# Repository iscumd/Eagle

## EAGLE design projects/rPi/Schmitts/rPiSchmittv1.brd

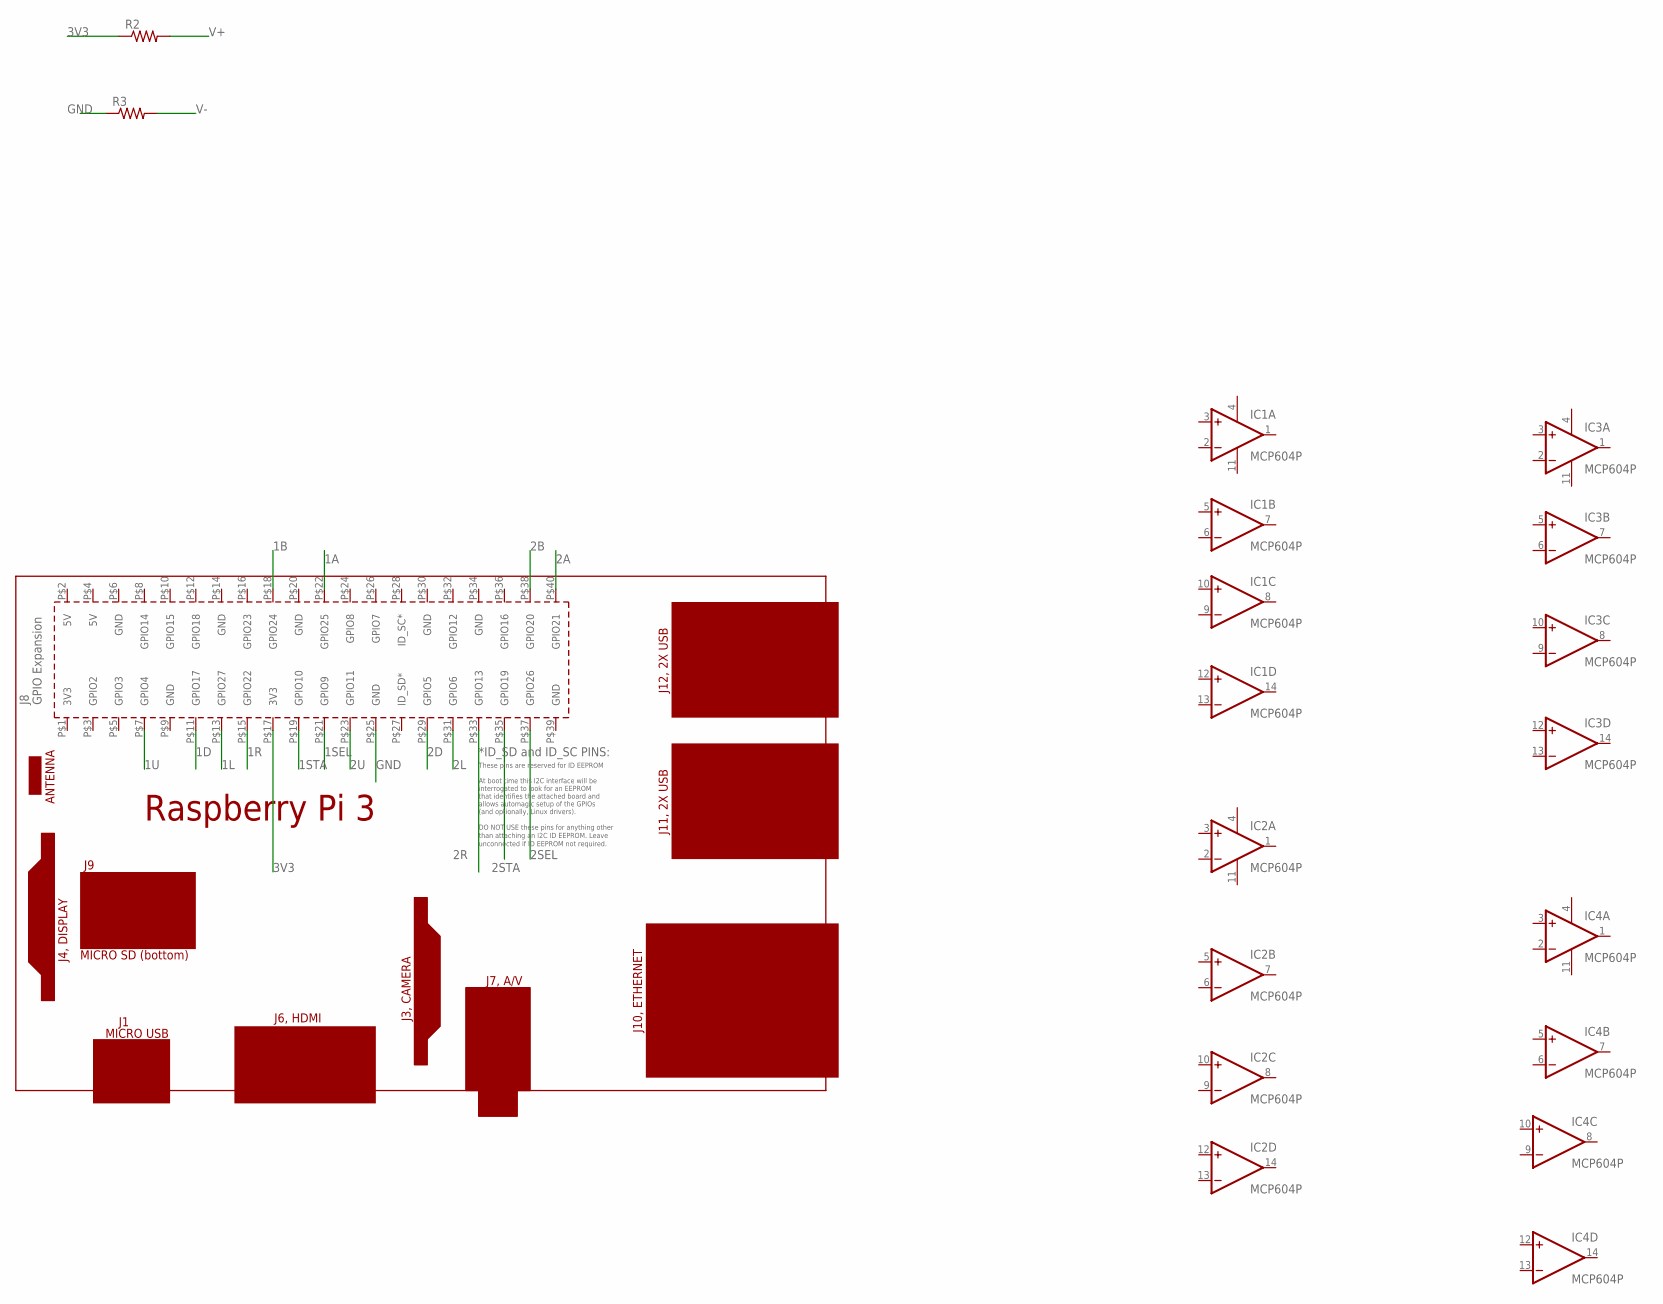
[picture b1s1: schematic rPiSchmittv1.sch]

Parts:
IC1, IC2, IC3, IC4: MCP604P; DIL14
PCB1: RPI3
R2, R3: RESISTOR0603-RES; 0603-RES

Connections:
1A: PCB1.P$22 (GPIO25)
1B: PCB1.P$18 (GPIO24)
1D: PCB1.P$11 (GPIO17)
1L: PCB1.P$13 (GPIO27)
1R: PCB1.P$15 (GPIO22)
1SEL: PCB1.P$21 (GPIO9)
1STA: PCB1.P$19 (GPIO10)
1U: PCB1.P$7 (GPIO4)
2A: PCB1.P$40 (GPIO21)
2B: PCB1.P$38 (GPIO20)
2D: PCB1.P$29 (GPIO5)
2L: PCB1.P$31 (GPIO6)
2R: PCB1.P$33 (GPIO13)
2SEL: PCB1.P$37 (GPIO26)
2STA: PCB1.P$35 (GPIO19)
2U: PCB1.P$23 (GPIO11)
3V3: PCB1.P$17 (3V3), R2.1
GND: PCB1.P$25 (GND), R3.1
V+: IC1.4 (V+), IC2.4 (V+), IC3.4 (V+), IC4.4 (V+), R2.2
V-: IC1.11 (V-), IC2.11 (V-), IC3.11 (V-), IC4.11 (V-), R3.2

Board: 2 copper layers, 8 parts (0 on the bottom side), 4 nets, no tracks yet.

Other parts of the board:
R1: 0603-RES

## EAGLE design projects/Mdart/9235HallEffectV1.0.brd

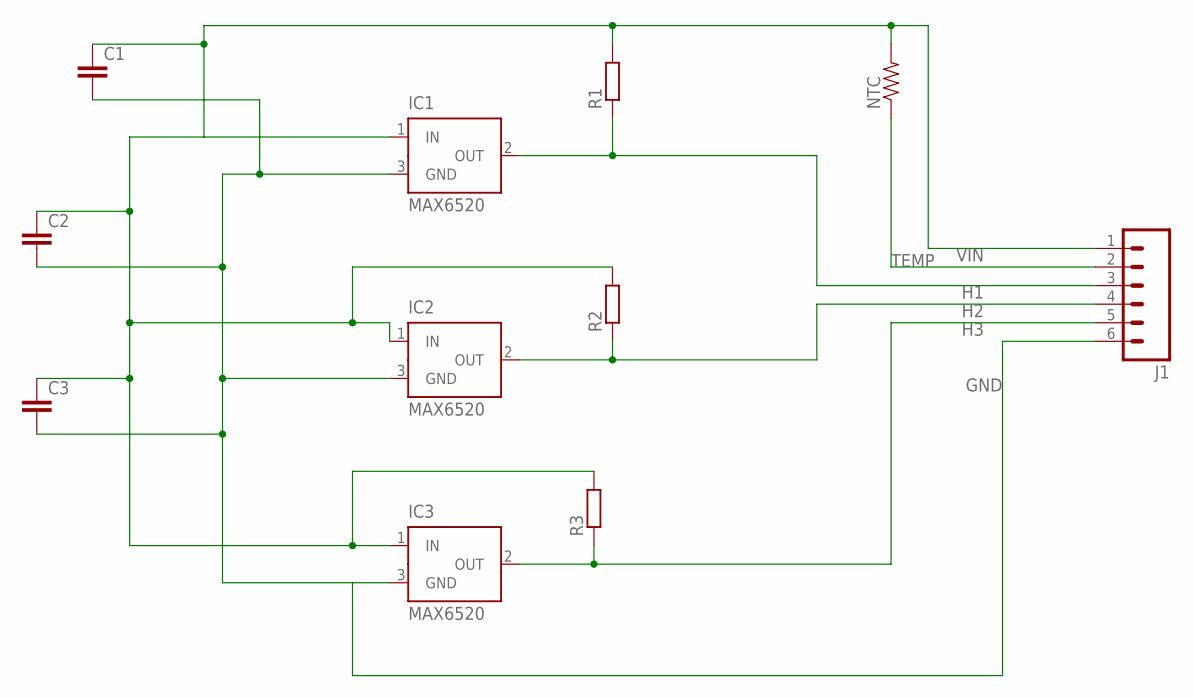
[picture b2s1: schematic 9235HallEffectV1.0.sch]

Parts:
C1, C2, C3: C-EUC0603; C0603
IC1, IC2, IC3: MAX6520; SOT23
J1: M06SMD-1MM; 1X06-1MM
NTC: RESISTOR0603-RES; 0603-RES
R1, R2, R3: RR0603; R0603

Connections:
GND: C1.2, C2.2, C3.2, IC1.3 (GND), IC2.3 (GND), IC3.3 (GND), J1.6
H1: IC1.2 (OUT), J1.3, R1.1
H2: IC2.2 (OUT), J1.4, R2.1
H3: IC3.2 (OUT), J1.5, R3.1
TEMP: J1.2, NTC.1
VIN: C1.1, C2.1, C3.1, IC1.1 (IN), IC2.1 (IN), IC3.1 (IN), J1.1, NTC.2, R1.2, R2.2, R3.2

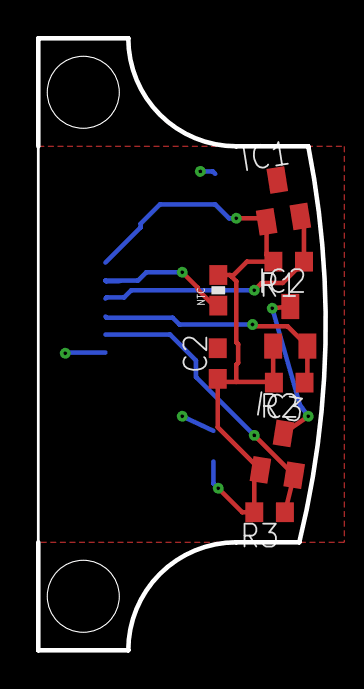
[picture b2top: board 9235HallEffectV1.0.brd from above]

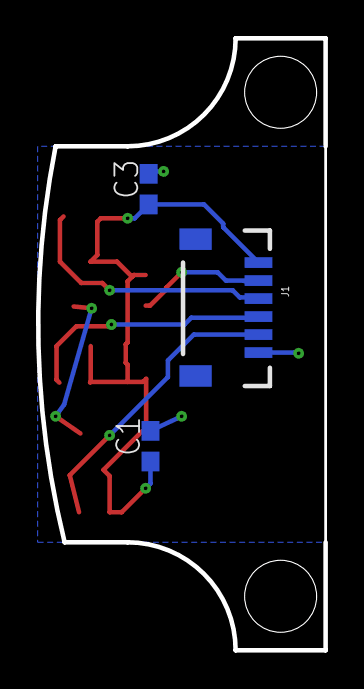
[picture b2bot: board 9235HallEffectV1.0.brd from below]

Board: 2 copper layers, 16.0 x 34.0 mm, 11 parts (3 on the bottom side), 6 nets.

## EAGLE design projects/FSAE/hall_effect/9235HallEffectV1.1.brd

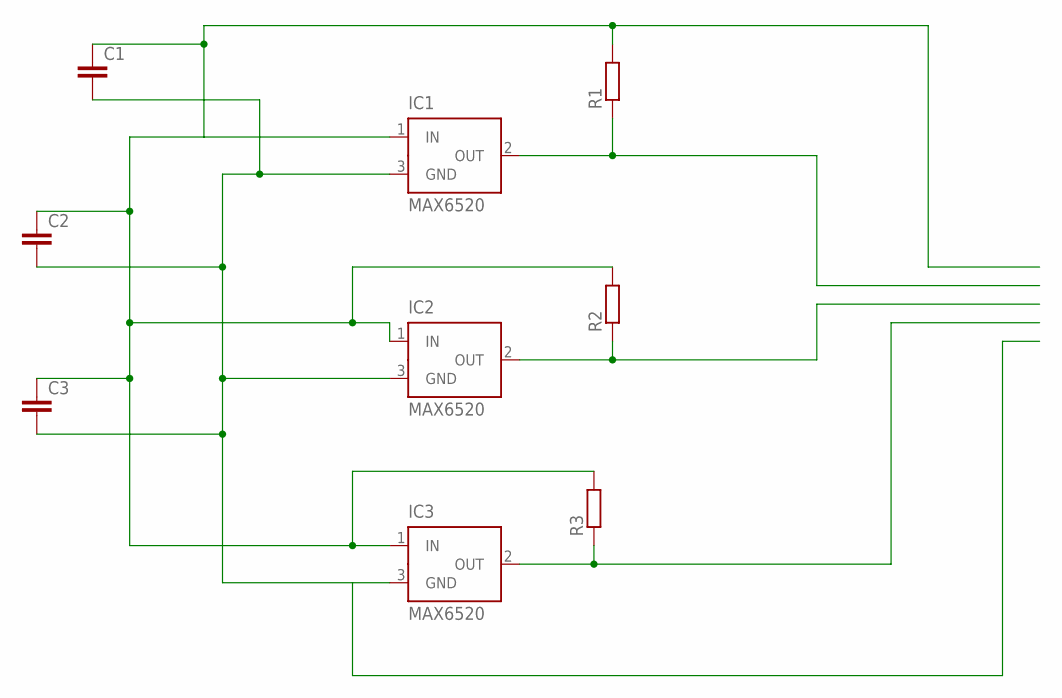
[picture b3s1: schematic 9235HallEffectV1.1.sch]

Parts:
C1, C2, C3: C-EUC0603; C0603
IC1, IC2, IC3: MAX6520; SOT23
R1, R2, R3: RR0603; R0603

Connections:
GND: C1.2, C2.2, C3.2, IC1.3 (GND), IC2.3 (GND), IC3.3 (GND)
H1: IC1.2 (OUT), R1.1
H2: IC2.2 (OUT), R2.1
H3: IC3.2 (OUT), R3.1
VIN: C1.1, C2.1, C3.1, IC1.1 (IN), IC2.1 (IN), IC3.1 (IN), R1.2, R2.2, R3.2

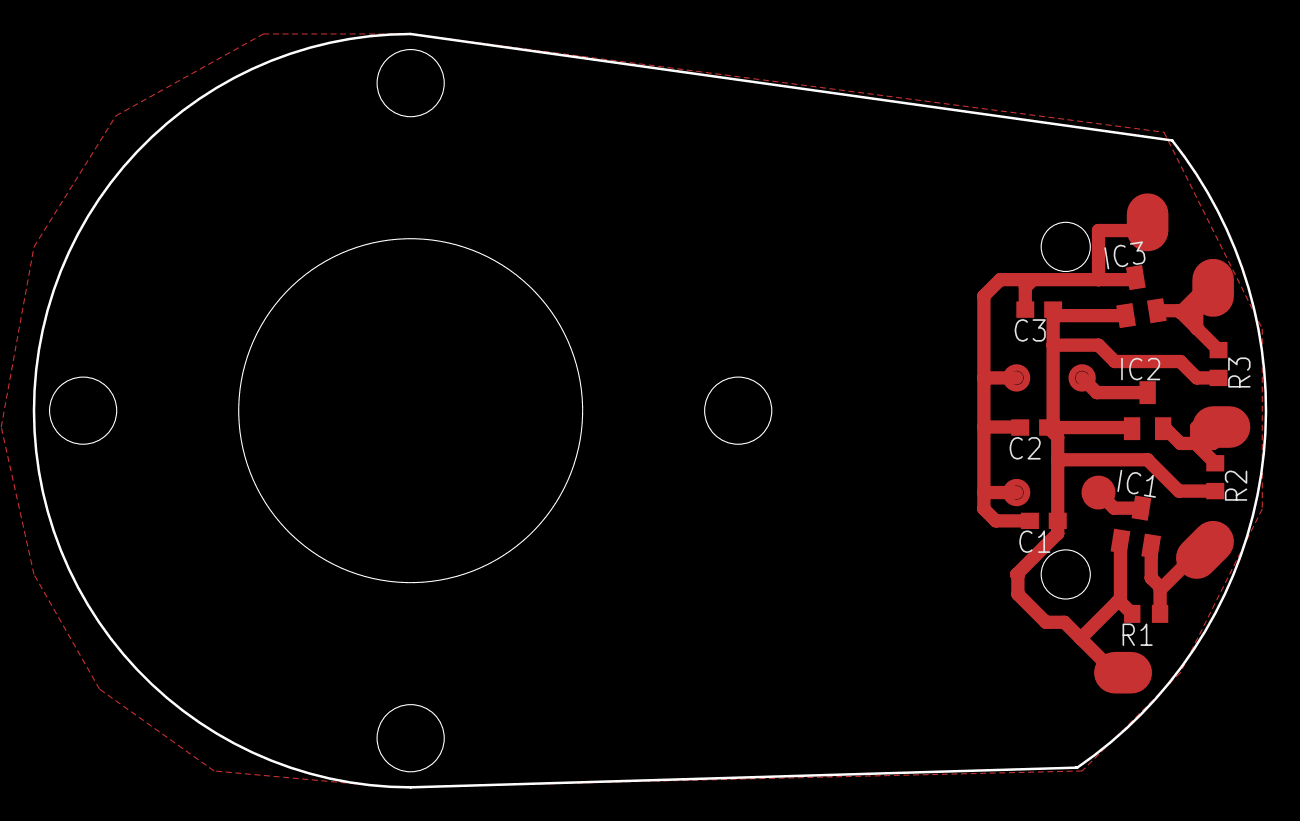
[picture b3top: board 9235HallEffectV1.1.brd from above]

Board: 2 copper layers, 75.2 x 46.0 mm, 9 parts (0 on the bottom side), 5 nets.

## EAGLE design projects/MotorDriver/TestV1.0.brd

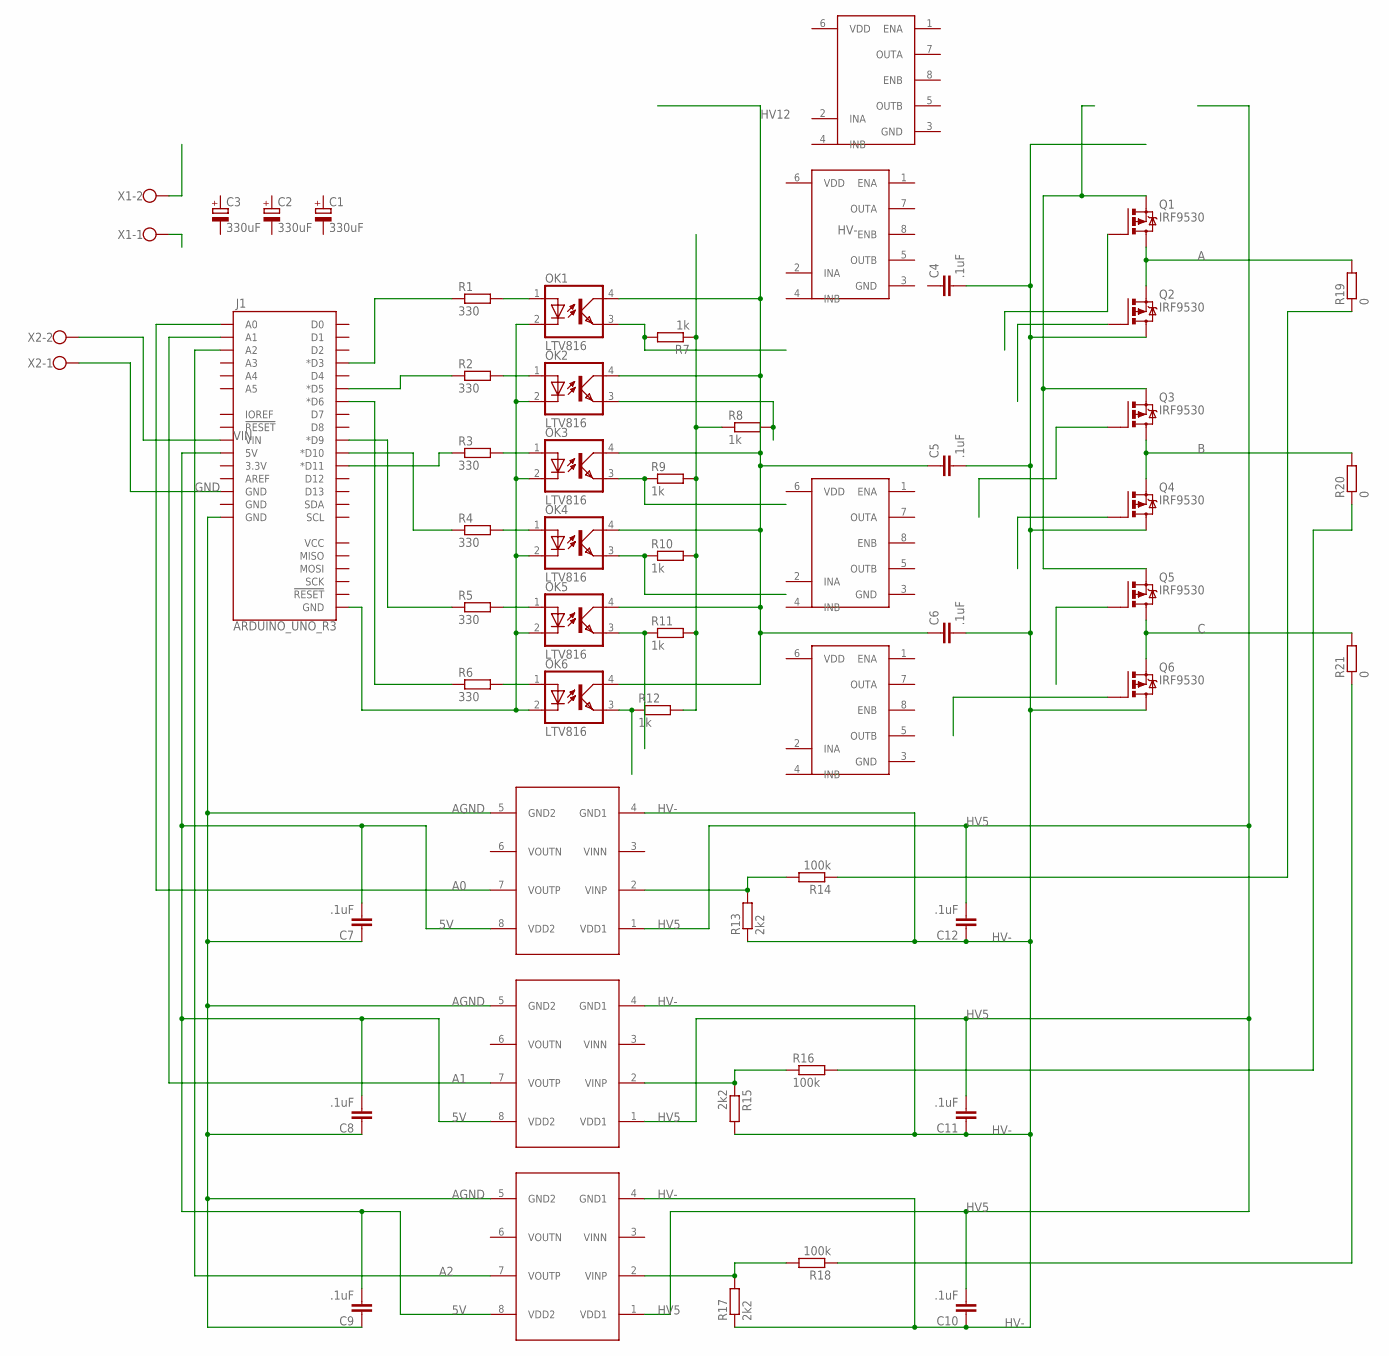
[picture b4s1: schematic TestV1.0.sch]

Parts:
C1, C2, C3: 330uF; E5-13
C4, C5, C6, C7, C8, C9, C10, C11, C12: .1uF; C0603
J1: ARDUINO_UNO_R3; ARDUINO_R3
MAX17604_A, MAX17604_B, MAX17604_C, MAX17604_D: MAX17604; SO08
OK1, OK2, OK3, OK4, OK5, OK6: LTV816; DIL04
Q1, Q2, Q3, Q4, Q5, Q6: IRF9530; TO220BV
R1, R2, R3, R4, R5, R6: 330; R0603
R7, R8, R9, R10, R11, R12: 1k; R0603
R13, R15, R17: 2k2; R0603
R14, R16, R18: 100k; R0603
R19, R20, R21: 0; R0603
U$7, U$8, U$9: AMC1200; SO08
X1, X2: SCREWCONNECTOR; 2PIN-SCREW-TERMINAL

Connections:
5V: C7.2, C8.2, C9.2, J1.5V, U$7.8 (VDD2), U$8.8 (VDD2), U$9.8 (VDD2)
A: Q1.D, Q2.S, R19.2
A0: J1.A0, U$7.7 (VOUTP)
A1: J1.A1, U$8.7 (VOUTP)
A2: J1.A2, U$9.7 (VOUTP)
AGND: C7.1, C8.1, C9.1, J1.GND@2 (GND), U$7.5 (GND2), U$8.5 (GND2), U$9.5 (GND2)
A_MINOR: R14.1, R19.1
B: Q3.D, Q4.S, R20.2
B_MINOR: R16.2, R20.1
C: Q5.D, Q6.S, R21.2
C_MINOR: R18.1, R21.1
GND: J1.GND@4 (GND), X2.1
HV5: C10.2, C11.2, C12.2, U$7.1 (VDD1), U$8.1 (VDD1), U$9.1 (VDD1)
HV12: C5.1, C6.1, OK1.4 (COL), OK2.4 (COL), OK3.4 (COL), OK4.4 (COL), OK5.4 (COL), OK6.4 (COL)
HV+: Q1.S, Q3.S, Q5.S
HV-: C4.2, C5.2, C6.2, C10.1, C11.1, C12.1, Q2.D, Q4.D, Q6.D, R13.1, R15.2, R17.1, U$7.4 (GND1), U$8.4 (GND1), U$9.4 (GND1)
unnamed: OK1.3 (EMIT), R7.2
unnamed: OK2.3 (EMIT), R8.2
unnamed: OK3.3 (EMIT), R9.1
unnamed: OK4.3 (EMIT), R10.1
unnamed: OK5.3 (EMIT), R11.1
unnamed: OK6.3 (EMIT), R12.1
unnamed: OK1.1 (A), R1.2
unnamed: J1.D3 (*D3), R1.1
unnamed: J1.GND@1 (GND), OK1.2 (C), OK2.2 (C), OK3.2 (C), OK4.2 (C), OK5.2 (C), OK6.2 (C)
unnamed: OK6.1 (A), R6.2
unnamed: OK5.1 (A), R5.2
unnamed: OK4.1 (A), R4.2
unnamed: OK3.1 (A), R3.2
unnamed: OK2.1 (A), R2.2
unnamed: J1.D5 (*D5), R2.1
unnamed: J1.D10 (*D10), R4.1
unnamed: J1.D11 (*D11), R3.1
unnamed: J1.D9 (*D9), R5.1
unnamed: J1.D6 (*D6), R6.1
unnamed: R13.2, R14.2, U$7.2 (VINP)
unnamed: R15.1, R16.1, U$8.2 (VINP)
unnamed: R17.2, R18.2, U$9.2 (VINP)
unnamed: R7.1, R8.1, R9.2, R10.2, R11.2, R12.2
VIN: J1.VIN, X2.2

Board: 2 copper layers, 55 parts (1 on the bottom side), 40 nets, no tracks yet.

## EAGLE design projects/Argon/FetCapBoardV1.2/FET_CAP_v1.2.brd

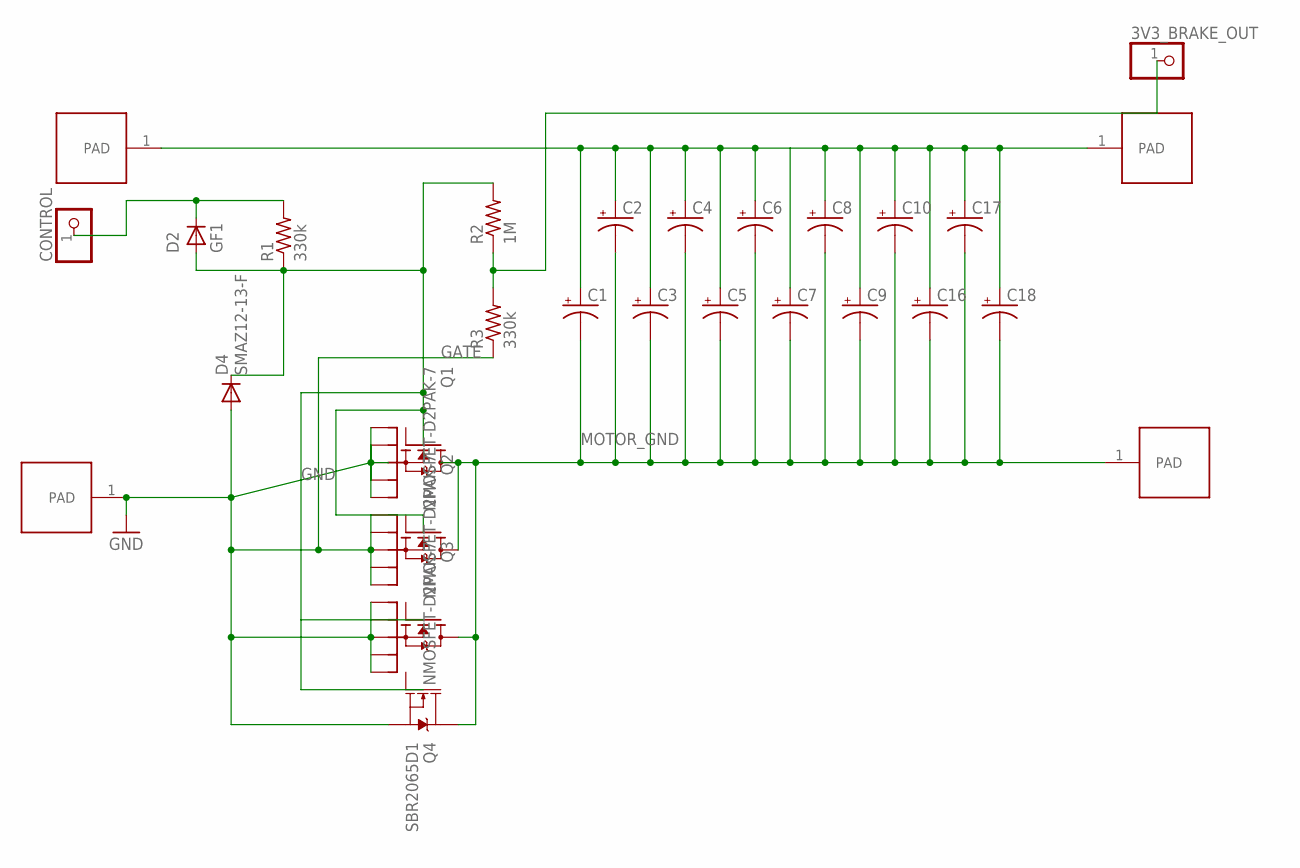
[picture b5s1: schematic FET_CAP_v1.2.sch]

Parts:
3V3_BRAKE_OUT: PINHD-1X1; 1X01
C1, C2, C3, C4, C5: CPOL-USE3.5-8; E3,5-8
C6, C7, C8, C9, C10, C16, C17, C18: CPOL-USE5-13; E5-13
CONTROL: PINHD-1X1; 1X01
D2: GF1; SMA-DO214AC
D4: SMAZ12-13-F; DO-214AC
Q1, Q2, Q3: NMOSFET-D2PAK-7; D2PAK-7
Q4: SBR2065D1; DPAK
R1, R3: 330k; R0603
R2: 1M; R0603
U$1, U$2, U$3, U$4: WIRE_SOLDER_PAD; SOLDER_PAD

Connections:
3.3V_OUT: 3V3_BRAKE_OUT.1, R2.1, R3.2
GATE: D2.A, D4.C, R1.1, R2.2
GND: D4.A, Q1.S1, Q1.S2, Q1.S3, Q1.S4, Q1.S5, Q2.S1, Q2.S5, Q3.S1, Q3.S5, Q4.3 (S), R3.1, U$4.1
MOTOR_GND: C1.-, C2.-, C3.-, C4.-, C5.-, C6.-, C7.-, C8.-, C9.-, C10.-, C16.-, C17.-, C18.-, Q1.D, Q2.D, Q3.D, Q4.4 (D), U$3.1
unnamed: CONTROL.1, D2.K (C), R1.2
V_BATT: C1.+, C2.+, C3.+, C4.+, C5.+, C6.+, C7.+, C8.+, C9.+, C10.+, C16.+, C17.+, C18.+, U$1.1, U$2.1

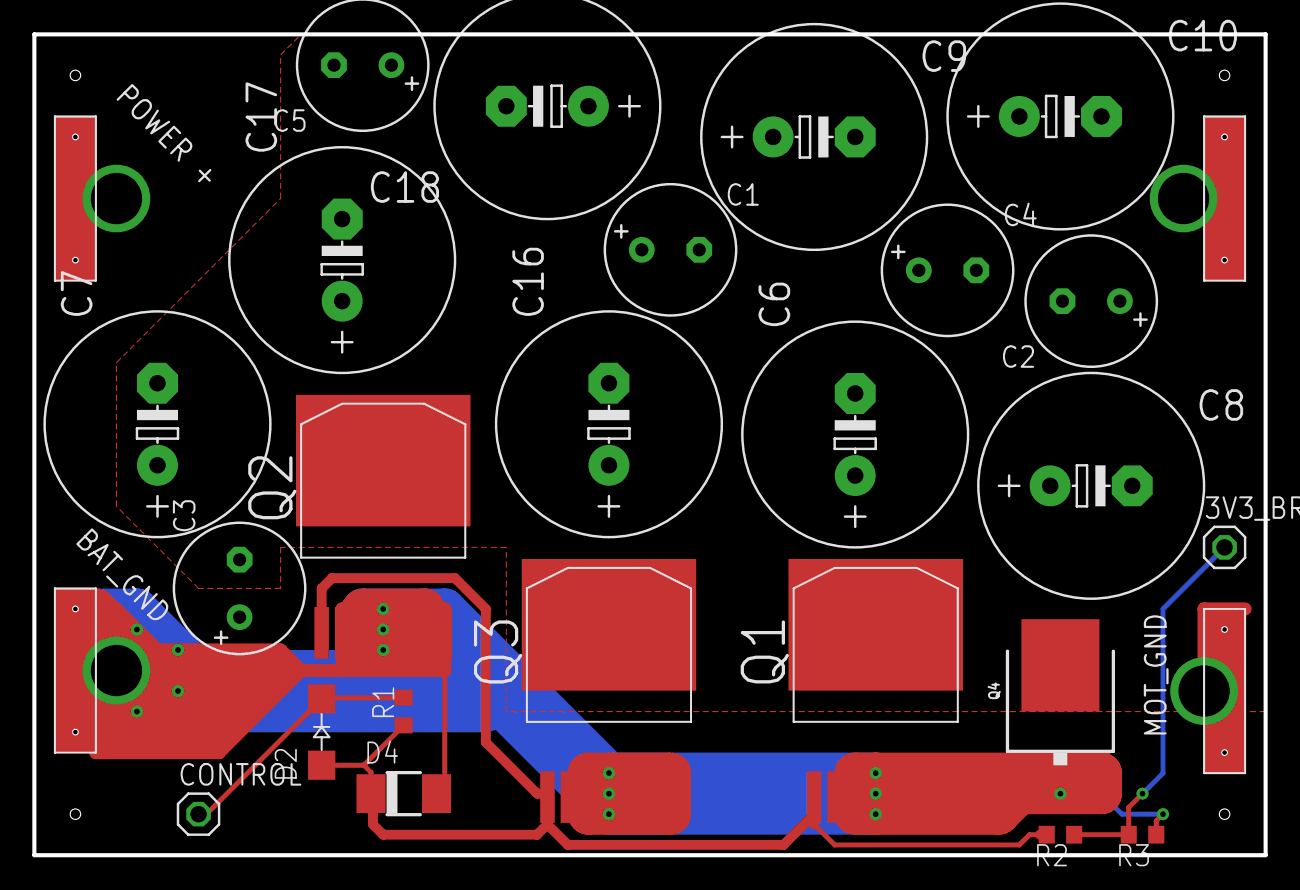
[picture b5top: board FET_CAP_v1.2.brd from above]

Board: 2 copper layers, 76.2 x 50.8 mm, 28 parts (0 on the bottom side), 6 nets.

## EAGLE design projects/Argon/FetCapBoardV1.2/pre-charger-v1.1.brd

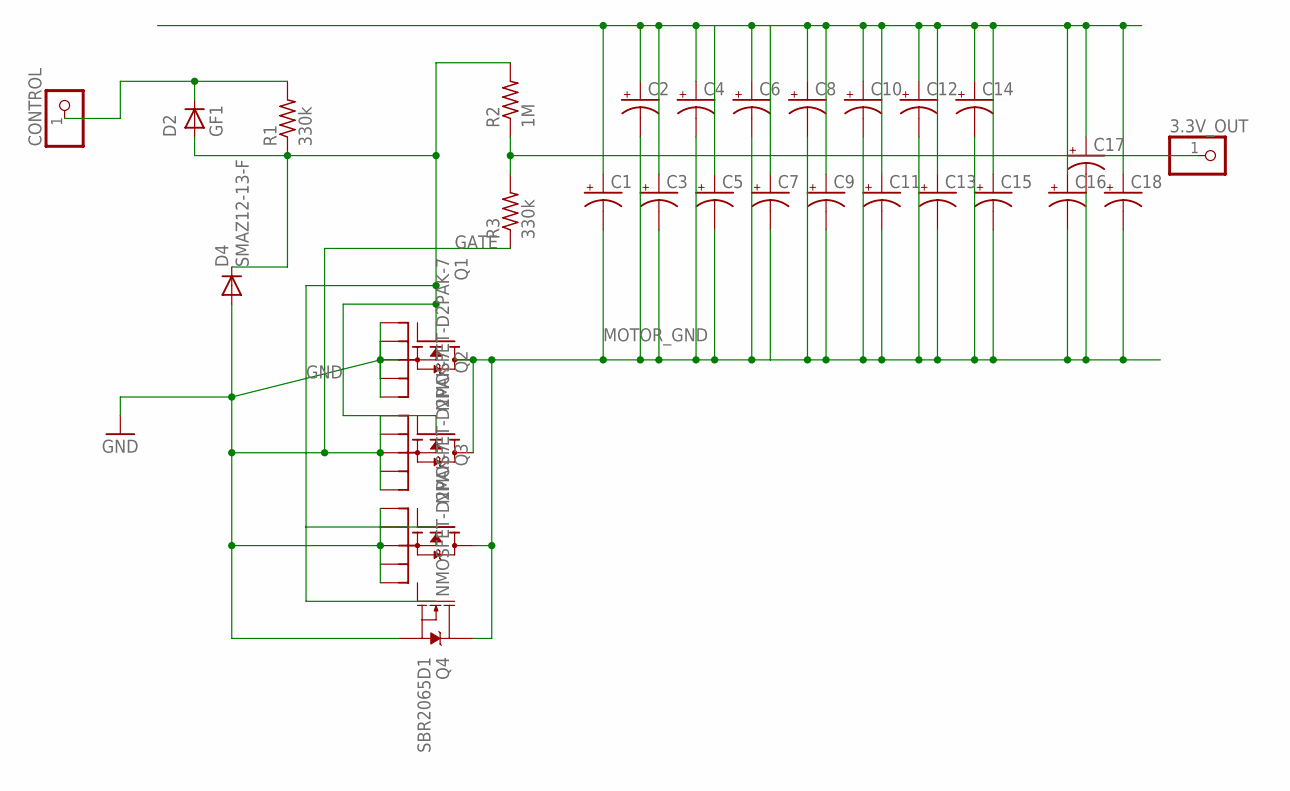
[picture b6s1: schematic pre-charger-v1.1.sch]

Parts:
3.3V_OUT: PINHD-1X1; 1X01
C1, C2, C3, C4, C5, C6, C7, C8, C9, C10, C11, C12, C13, C14, C15: CPOL-USE3.5-8; E3,5-8
C16, C17, C18: CPOL-USE5-13; E5-13
CONTROL: PINHD-1X1; 1X01
D2: GF1; SMA-DO214AC
D4: SMAZ12-13-F; DO-214AC
Q1, Q2, Q3: NMOSFET-D2PAK-7; D2PAK-7
Q4: SBR2065D1; DPAK
R1, R3: 330k; R0603
R2: 1M; R0603

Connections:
3.3V_OUT: 3.3V_OUT.1, R2.1, R3.2
GATE: D2.A, D4.C, R1.1, R2.2
GND: D4.A, Q1.S1, Q1.S2, Q1.S3, Q1.S4, Q1.S5, Q2.S1, Q2.S5, Q3.S1, Q3.S5, Q4.3 (S), R3.1
MOTOR_GND: C1.-, C2.-, C3.-, C4.-, C5.-, C6.-, C7.-, C8.-, C9.-, C10.-, C11.-, C12.-, C13.-, C14.-, C15.-, C16.-, C17.-, C18.-, Q1.D, Q2.D, Q3.D, Q4.4 (D)
unnamed: CONTROL.1, D2.K (C), R1.2
V_BATT: C1.+, C2.+, C3.+, C4.+, C5.+, C6.+, C7.+, C8.+, C9.+, C10.+, C11.+, C12.+, C13.+, C14.+, C15.+, C16.+, C17.+, C18.+

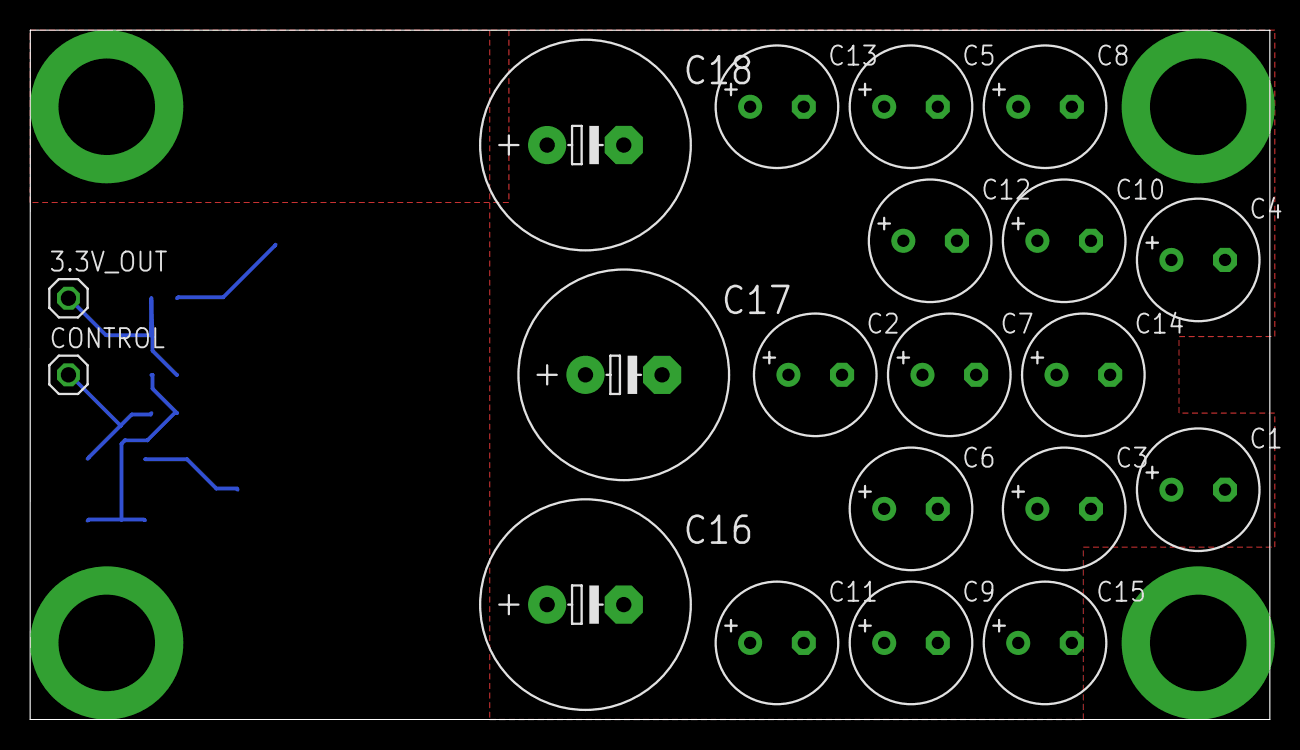
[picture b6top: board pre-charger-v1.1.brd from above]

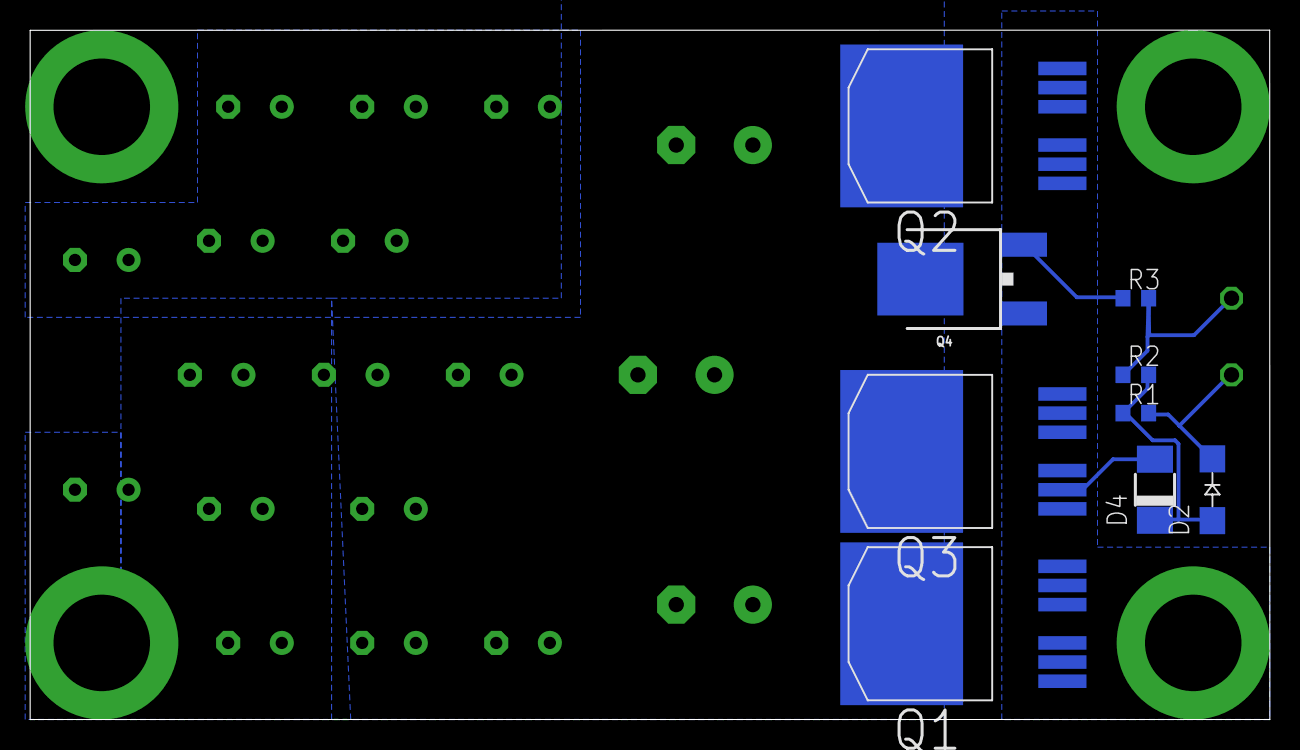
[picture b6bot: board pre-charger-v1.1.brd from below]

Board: 2 copper layers, 82.2 x 45.7 mm, 29 parts (9 on the bottom side), 6 nets.

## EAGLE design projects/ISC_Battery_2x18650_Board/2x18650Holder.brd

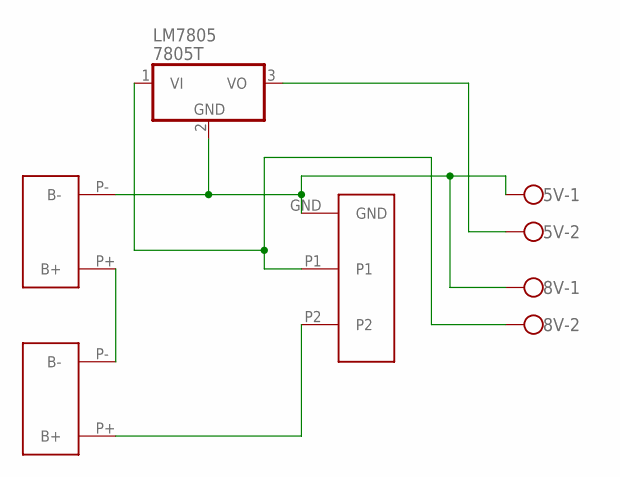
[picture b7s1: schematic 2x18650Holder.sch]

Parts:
5V, 8V: SCREWCONNECTOR; 2PIN-SCREW-TERMINAL
LM7805: 7805T; TO220H
U$1, U$2: BATTERY
U$3: ROCKER

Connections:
GND: 5V.1, 8V.1, LM7805.2 (GND), U$2.P- (B-), U$3.GND
unnamed: 5V.2, LM7805.3 (VO)
unnamed: 8V.2, LM7805.1 (VI), U$3.P1
unnamed: U$1.P- (B-), U$2.P+ (B+)
unnamed: U$1.P+ (B+), U$3.P2

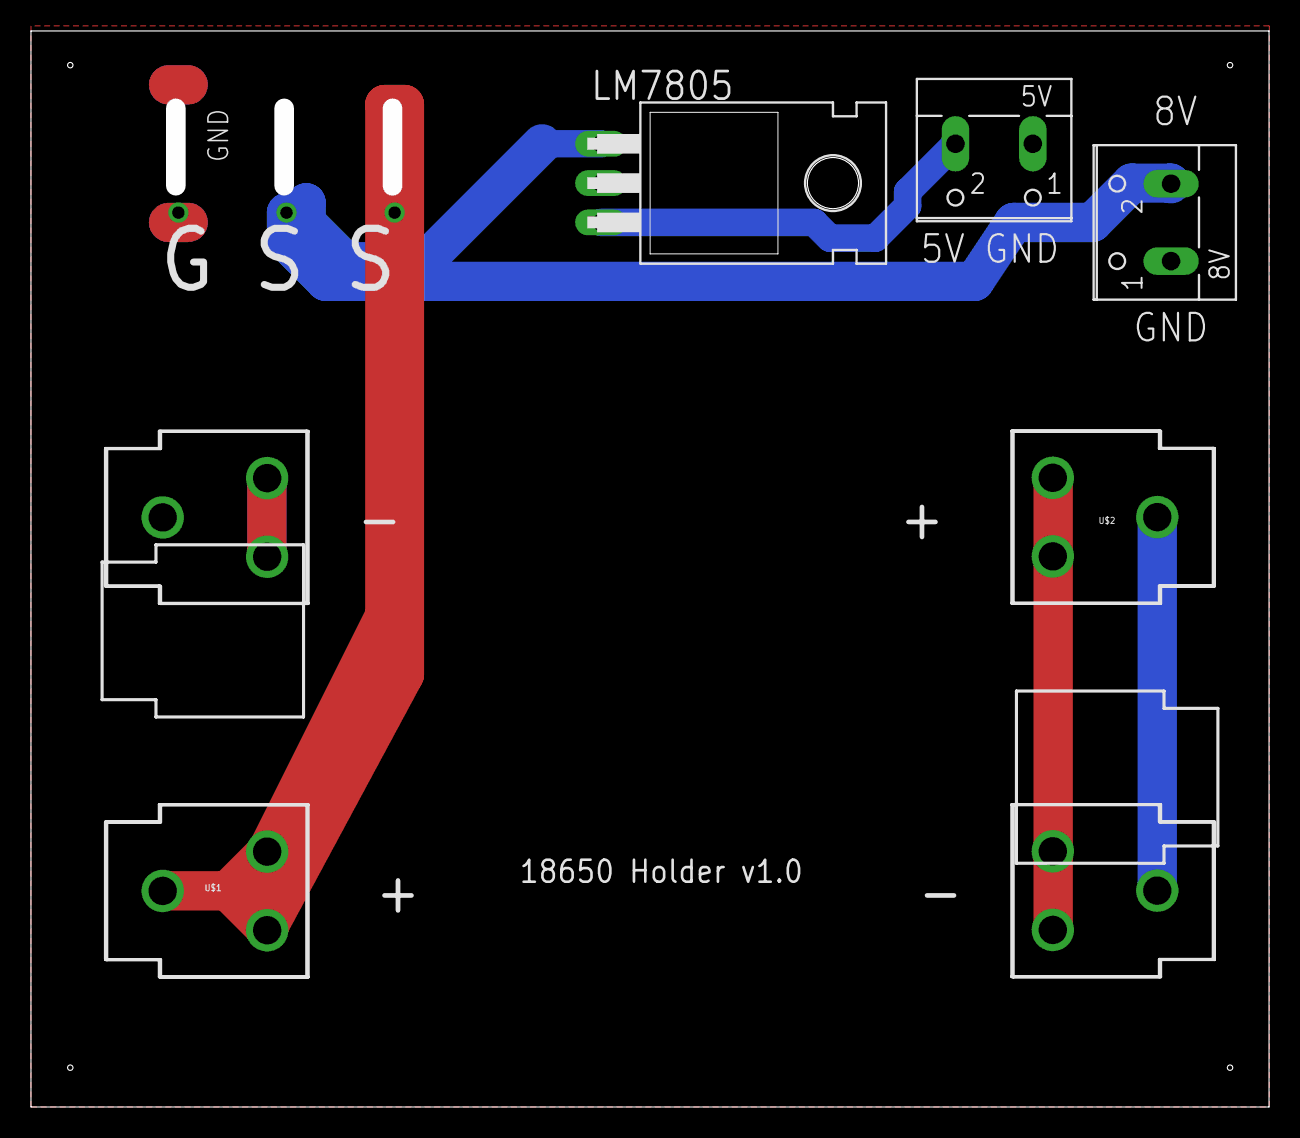
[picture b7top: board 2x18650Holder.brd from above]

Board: 2 copper layers, 78.7 x 68.2 mm, 6 parts (0 on the bottom side), 5 nets.

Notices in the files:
parts and their libraries:
SparkFun-DiscreteSemi: Licensing: Creative Commons ShareAlike 4.0 International - https://creativecommons.org/licenses/by-sa/4.0
